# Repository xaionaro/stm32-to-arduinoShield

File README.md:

STM32 boards for fast prototyping

Original repository: [https://embed.life/dyokunev/stm32-to-arduinoShield](https://embed.life/dyokunev/stm32-to-arduinoShield)

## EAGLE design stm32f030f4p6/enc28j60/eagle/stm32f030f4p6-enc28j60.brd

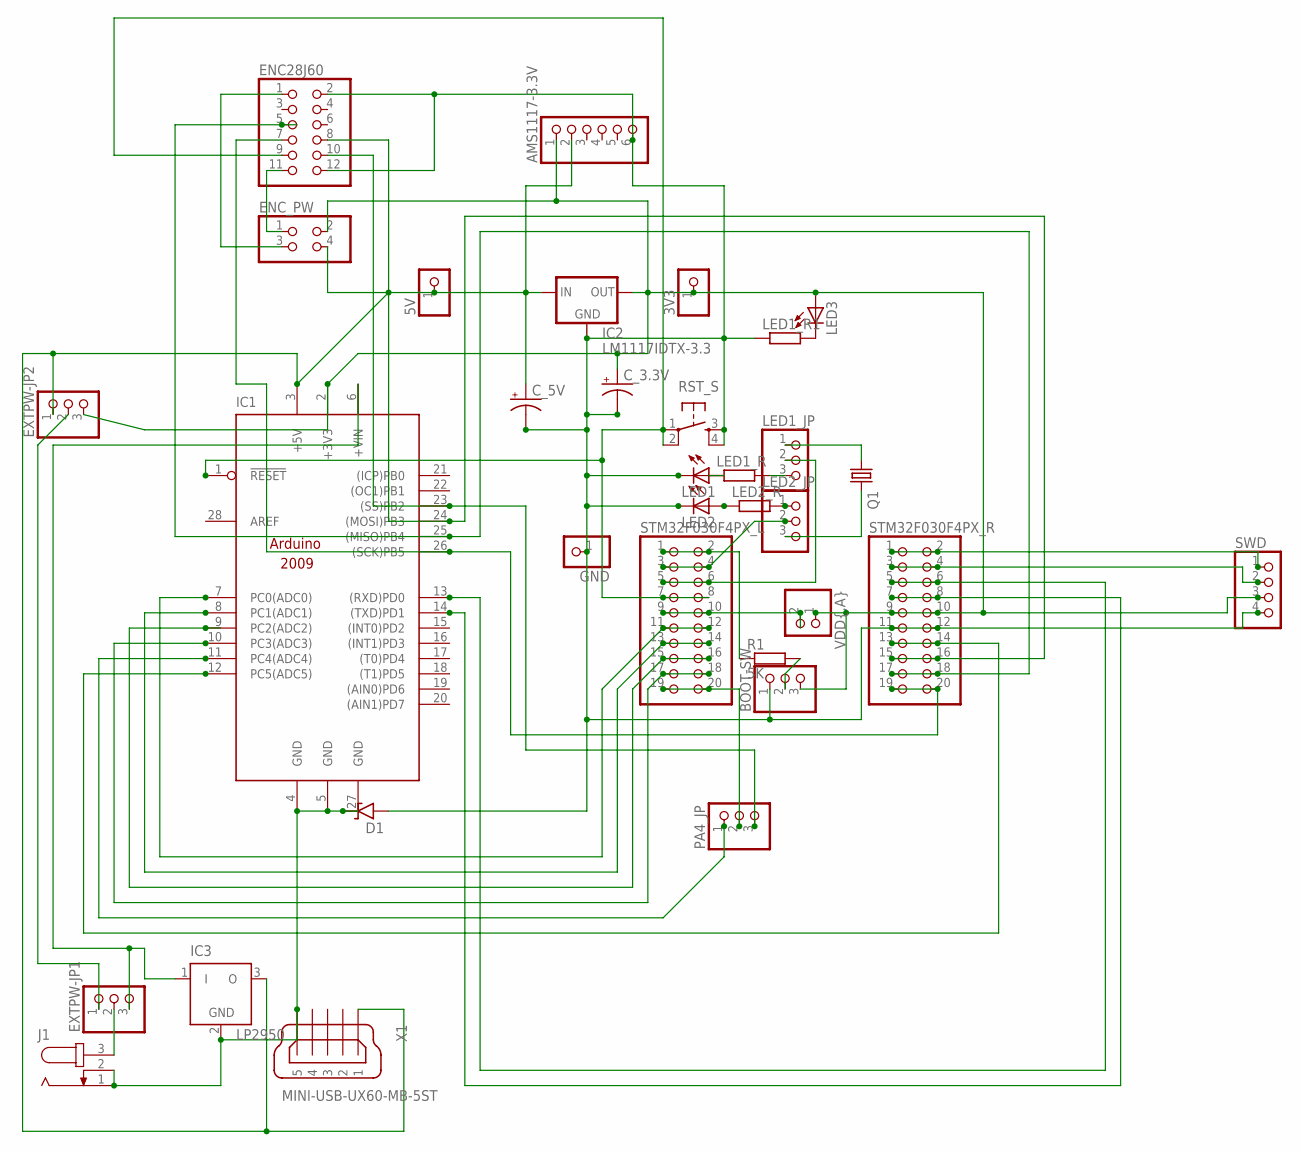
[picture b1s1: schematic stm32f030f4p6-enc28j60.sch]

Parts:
3V3, 5V: PINHD-1X1_2.00; 1X01M
AMS1117-3.3V: PINHD-1X06_2.54; 1X06
BOOT-SW: PINHD-1X3; 1X03
C_3.3V, C_5V: CPOL-USE3.5-8; E3,5-8
D1: 1N9ZENER2; DO35-2
ENC28J60: PINHD-2X6_2.54; 2X06
ENC_PW: PINHD-2X2_2.54; 2X02
EXTPW-JP1, EXTPW-JP2: PINHD-1X3; 1X03
GND: PINHD-1X1_2.00; 1X01M
IC1: ARDUINO2009_PIN_12; ARDUINO2009_2
IC2: LM1117IDTX-3.3; TO252
IC3: LP2950; DPACK
J1: JACK-PLUG0; SPC4077
LED1, LED2, LED3: LED_ELD260; LED_LD260
LED1_JP, LED2_JP: PINHD-1X3_2.54; 1X03
LED1_R, LED1_R1, LED2_R: R-EU_0204/7; 0204/7
PA4_JP: PINHD-1X3_2.54; 1X03
Q1: CRYSTALHC49S; HC49/S
R1: 5K; 0204/5
RST_S: TAC_SWITCHPTH; TACTILE-PTH
STM32F030F4PX_L, STM32F030F4PX_R: PINHD-2X10; 2X10
SWD: PINHD-1X4; 1X04
VDD{,A}: PINHD-1X2; 1X02
X1: MINI-USB-UX60-MB-5ST; UX60-MB-5ST

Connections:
3V3@EXT: ENC28J60.11, ENC_PW.1
5V: 5V.1, AMS1117-3.3V.2, C_5V.+, ENC_PW.4, EXTPW-JP2.1, IC1.3 (+5V), IC2.2 (IN), IC3.3 (O), X1.1
5V@EXT: ENC28J60.1, ENC_PW.3
BOOT: R1.1, STM32F030F4PX_L.1, STM32F030F4PX_L.2
BOOT@R: BOOT-SW.2, R1.2
GND@0: AMS1117-3.3V.6, BOOT-SW.1, C_3.3V.-, C_5V.-, D1.A, ENC28J60.2, ENC28J60.12, GND.1, IC2.1 (GND), LED1.K (C), LED1_R1.1, LED2.K (C), RST_S.3, RST_S.4, STM32F030F4PX_R.11, STM32F030F4PX_R.12, SWD.4
GND_RAW: D1.C, IC1.4 (GND), IC1.5 (GND), IC1.27 (GND), IC3.2 (GND), J1.1, J1.2, X1.5
unnamed: IC1.12 (PC5(ADC5)), STM32F030F4PX_R.13, STM32F030F4PX_R.14
unnamed: IC1.14 ((TXD)PD1), STM32F030F4PX_R.7, STM32F030F4PX_R.8
unnamed: IC1.13 ((RXD)PD0), STM32F030F4PX_R.5, STM32F030F4PX_R.6
unnamed: LED2.A, LED2_R.1
unnamed: LED1.A, LED1_R.1
unnamed: LED1_R1.2, LED3.K (C)
PA0: IC1.7 (PC0(ADC0)), STM32F030F4PX_L.11, STM32F030F4PX_L.12
PA1: IC1.8 (PC1(ADC1)), STM32F030F4PX_L.13, STM32F030F4PX_L.14
PA2: IC1.9 (PC2(ADC2)), STM32F030F4PX_L.15, STM32F030F4PX_L.16
PA3: IC1.10 (PC3(ADC3)), STM32F030F4PX_L.17, STM32F030F4PX_L.18
PA4: PA4_JP.2, STM32F030F4PX_L.19, STM32F030F4PX_L.20
PA4@L: IC1.11 (PC4(ADC4)), PA4_JP.1
PA4@R: ENC28J60.10, IC1.23 ((SS)PB2), PA4_JP.3
PA5_SCK: ENC28J60.7, IC1.26 ((SCK)PB5), STM32F030F4PX_R.19, STM32F030F4PX_R.20
PA6_MISO: ENC28J60.5, IC1.25 ((MISO)PB4), STM32F030F4PX_R.17, STM32F030F4PX_R.18
PA7_MOSI: ENC28J60.8, IC1.24 ((MOSI)PB3), STM32F030F4PX_R.15, STM32F030F4PX_R.16
PF0: LED2_JP.2, STM32F030F4PX_L.3, STM32F030F4PX_L.4
PF0@LED: LED2_JP.1, LED2_R.2
PF0@OCC: LED2_JP.3, Q1.2
PF1: LED1_JP.2, STM32F030F4PX_L.5, STM32F030F4PX_L.6
PF1@LED: LED1_JP.3, LED1_R.2
PF1@OCC: LED1_JP.1, Q1.1
RESET: ENC28J60.9, IC1.1 (!RESET), RST_S.1, RST_S.2, STM32F030F4PX_L.7, STM32F030F4PX_L.8
SWD_CLK: STM32F030F4PX_R.1, STM32F030F4PX_R.2, SWD.1
SWD_IO: STM32F030F4PX_R.3, STM32F030F4PX_R.4, SWD.2
VDD: 3V3.1, AMS1117-3.3V.1, BOOT-SW.3, C_3.3V.+, ENC_PW.2, EXTPW-JP2.3, IC1.2 (+3V3), IC2.TAB (OUT), LED3.A, STM32F030F4PX_R.9, STM32F030F4PX_R.10, SWD.3, VDD{,A}.1
VDDA: STM32F030F4PX_L.9, STM32F030F4PX_L.10, VDD{,A}.2
VIN: EXTPW-JP1.2, J1.3
VIN@HIGH: EXTPW-JP1.3, IC1.6 (+VIN), IC3.1 (I)
VIN@LOW: EXTPW-JP1.1, EXTPW-JP2.2

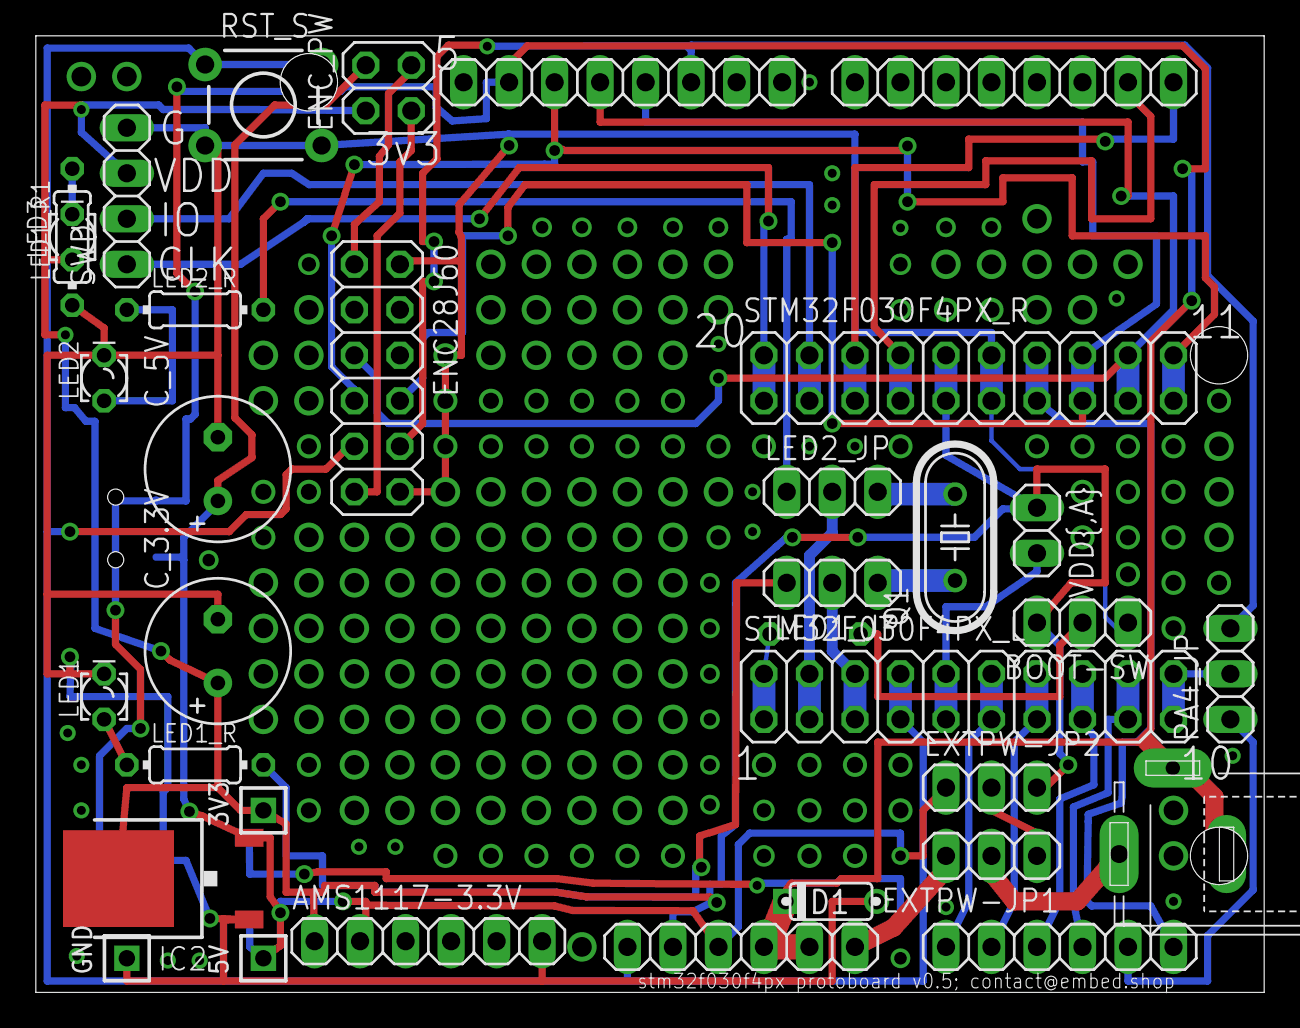
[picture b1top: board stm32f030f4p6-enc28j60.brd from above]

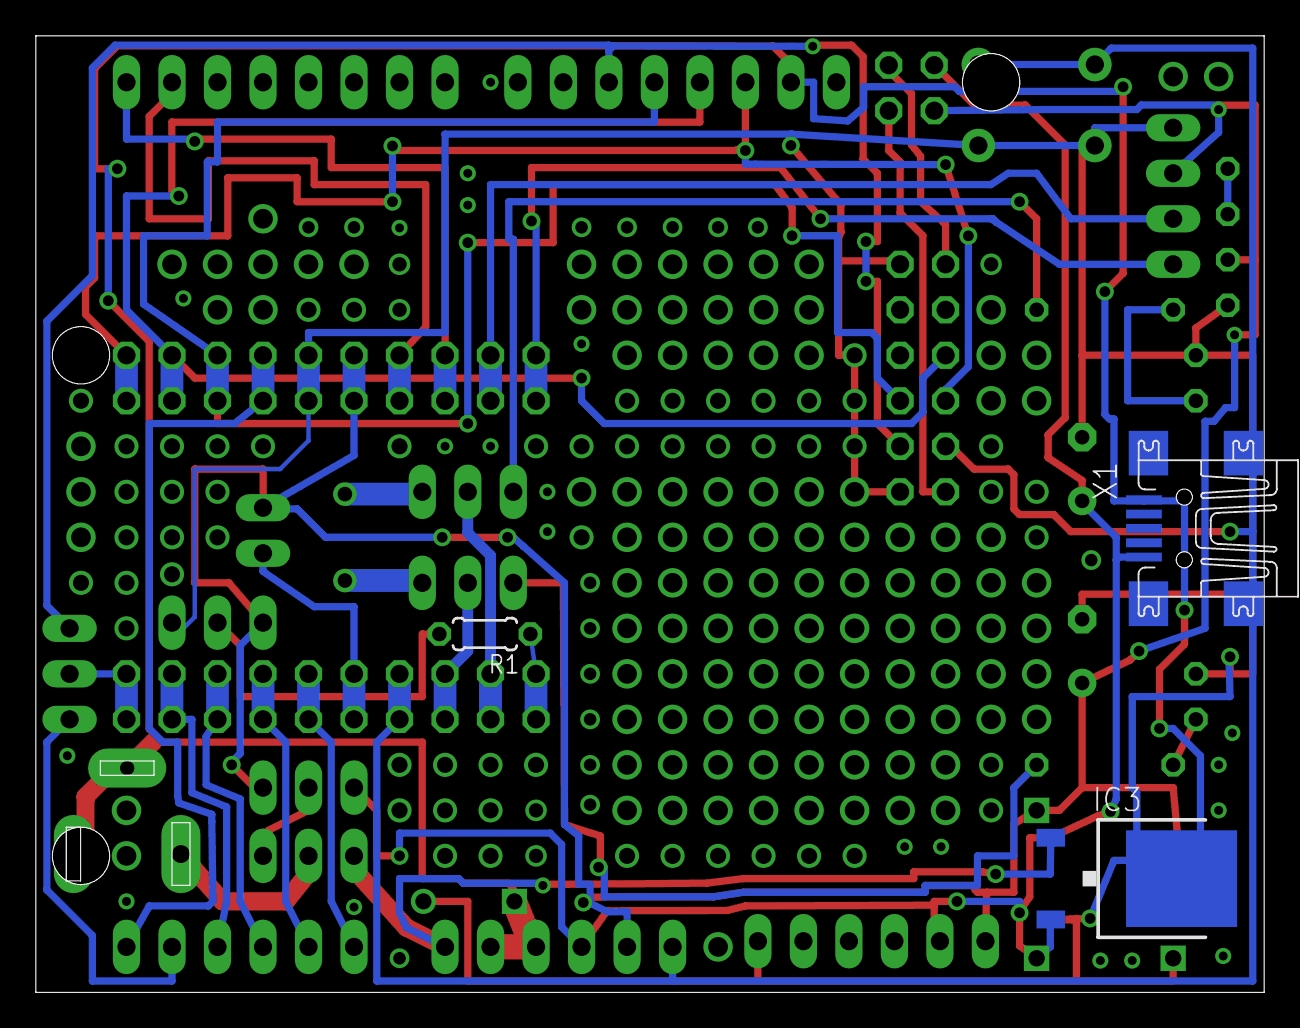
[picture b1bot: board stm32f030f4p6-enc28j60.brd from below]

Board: 2 copper layers, 68.6 x 53.4 mm, 33 parts (3 on the bottom side), 37 nets.

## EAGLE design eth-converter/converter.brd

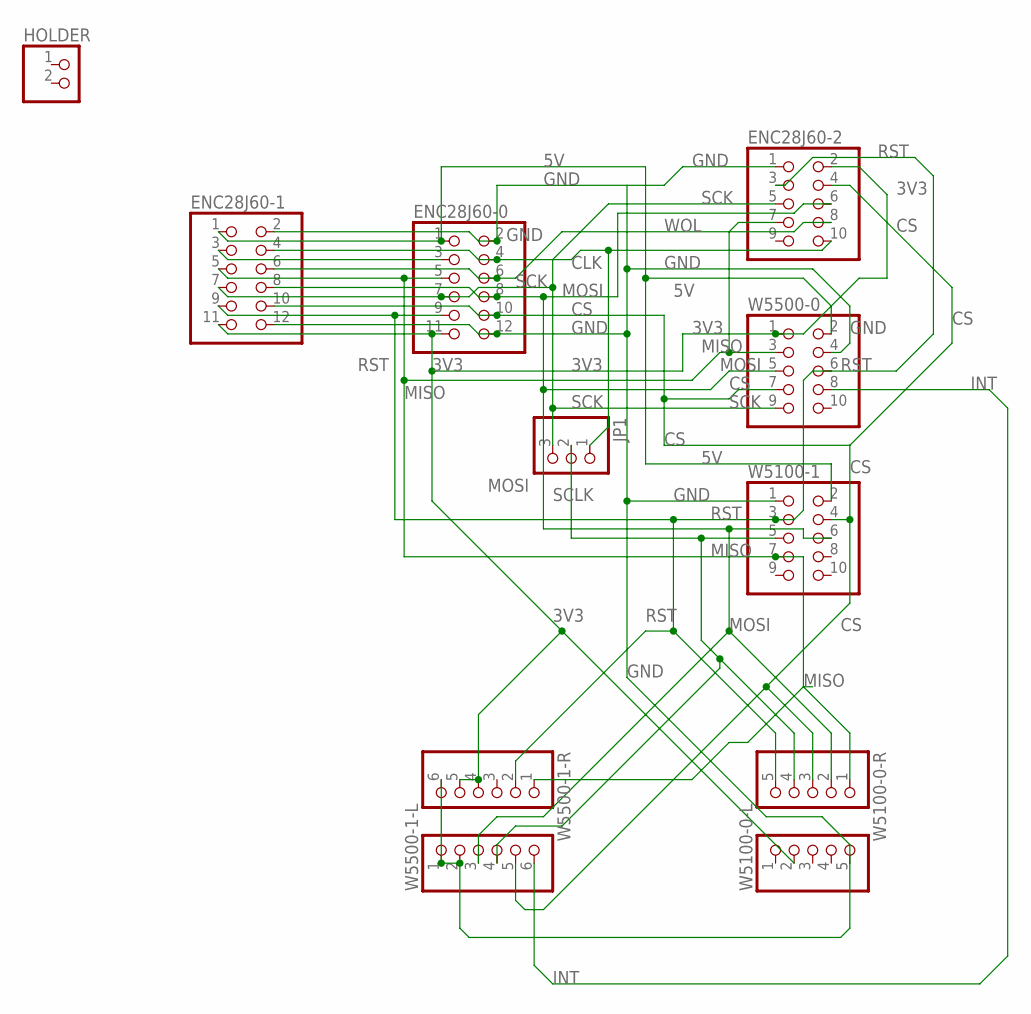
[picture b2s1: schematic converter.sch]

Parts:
ENC28J60-0, ENC28J60-1: PINHD-2X6; 2X06
ENC28J60-2: PINHD-2X5; 2X05
HOLDER: PINHD-1X2; 1X02
JP1: PINHD-1X3; 1X03
W5100-0-L, W5100-0-R: PINHD-1X5; 1X05
W5100-1, W5500-0: PINHD-2X5; 2X05
W5500-1-L, W5500-1-R: PINHD-1X6; 1X06

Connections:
3V3: ENC28J60-0.11, ENC28J60-1.11, ENC28J60-2.2, W5100-0-L.2, W5500-0.1, W5500-1-R.4, W5500-1-R.5
5V: ENC28J60-0.1, ENC28J60-1.1, W5100-1.2, W5500-0.2
CLK: ENC28J60-0.4, ENC28J60-1.4, ENC28J60-2.10, JP1.1
CS: ENC28J60-0.10, ENC28J60-1.10, ENC28J60-2.4, W5100-0-R.3, W5100-1.4, W5500-0.7, W5500-1-L.5
GND: ENC28J60-0.2, ENC28J60-0.12, ENC28J60-1.2, ENC28J60-1.12, ENC28J60-2.1, W5100-0-L.5, W5100-1.1, W5500-0.4, W5500-1-L.1, W5500-1-L.2, W5500-1-R.6
INT: W5500-0.8, W5500-1-L.6
MISO: ENC28J60-0.5, ENC28J60-1.5, ENC28J60-2.7, W5100-0-R.1, W5100-1.7, W5500-0.3
MOSI: ENC28J60-0.8, ENC28J60-1.8, ENC28J60-2.6, W5100-0-R.2, W5100-1.6, W5500-0.5, W5500-1-L.3
unnamed: ENC28J60-0.3, ENC28J60-1.3
RST: ENC28J60-0.9, ENC28J60-1.9, ENC28J60-2.3, W5100-0-R.5, W5100-1.3, W5500-0.6, W5500-1-R.2
SCK: ENC28J60-0.7, ENC28J60-1.7, ENC28J60-2.5, JP1.3, W5500-0.9
SCLK: JP1.2, W5100-0-R.4, W5100-1.5, W5500-1-L.4
WOL: ENC28J60-0.6, ENC28J60-1.6, ENC28J60-2.8

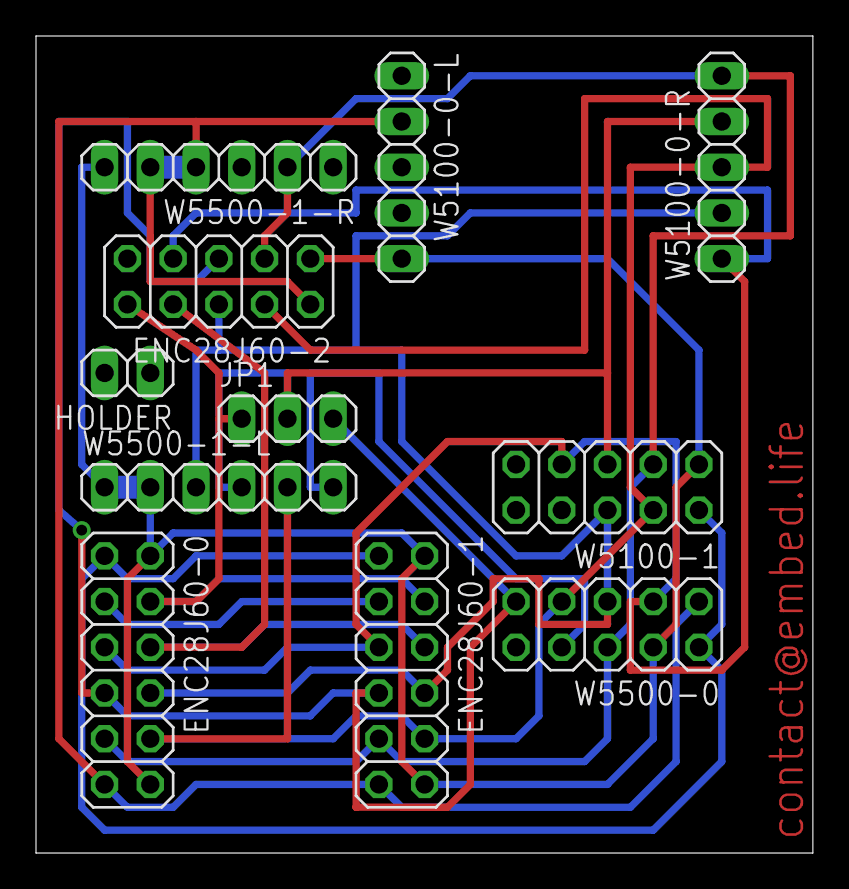
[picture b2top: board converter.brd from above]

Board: 2 copper layers, 43.2 x 45.4 mm, 11 parts (0 on the bottom side), 13 nets.

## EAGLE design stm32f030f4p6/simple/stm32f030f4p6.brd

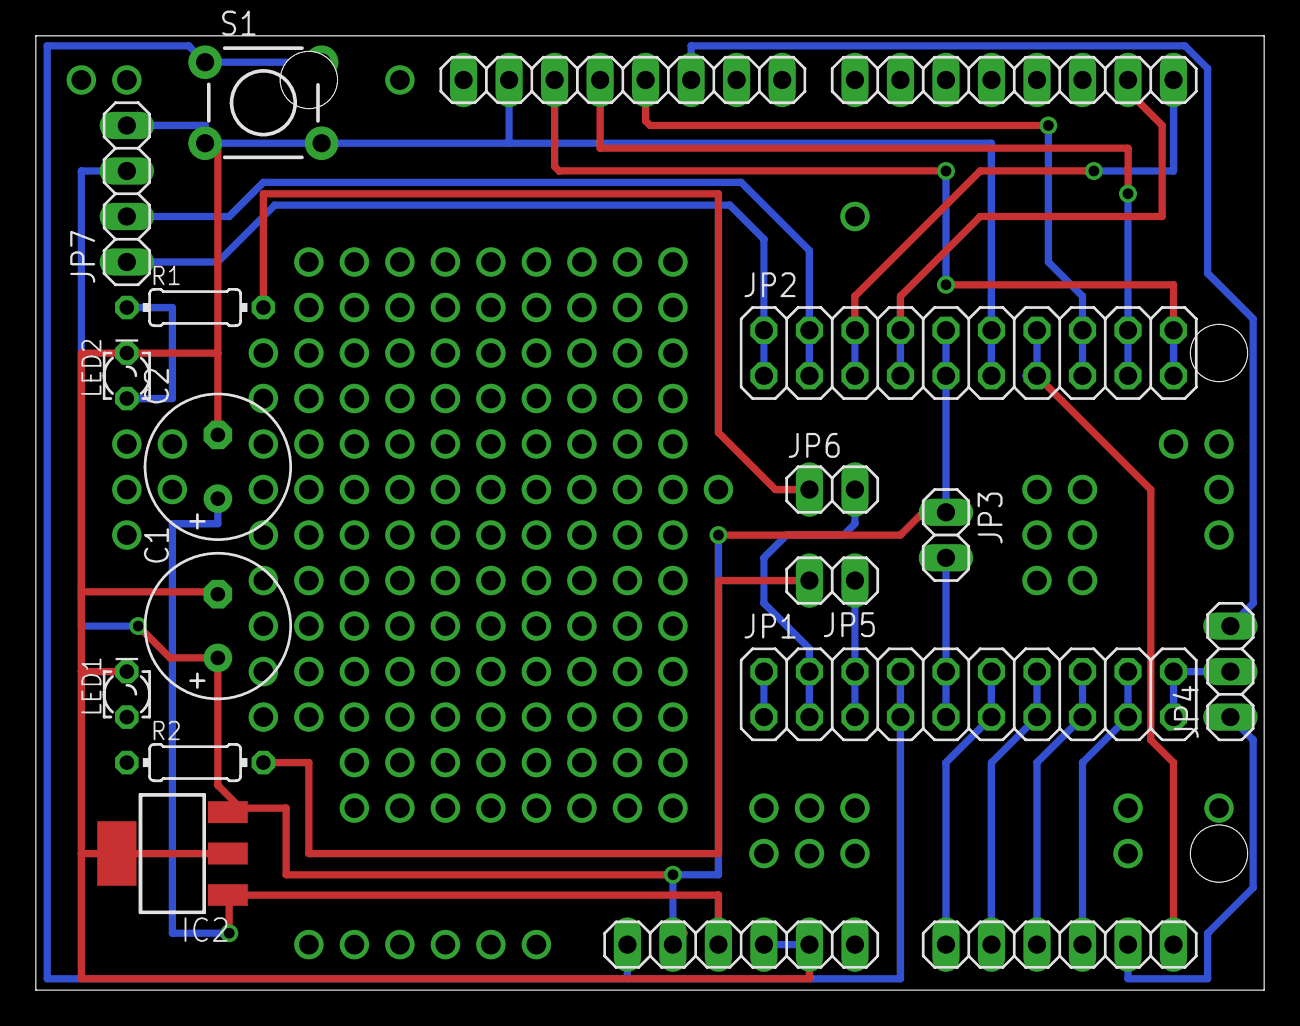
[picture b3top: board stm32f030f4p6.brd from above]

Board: 2 copper layers, 68.6 x 53.3 mm, 16 parts (0 on the bottom side), 27 nets.

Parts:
C1, C2: E3,5-8
IC1: ARDUINO2009_2
IC2: SOT223
JP1, JP2: 2X10
JP3, JP5, JP6: 1X02
JP4: 1X03
JP7: 1X04
LED1, LED2: LED_LD260
R1, R2: 0204/7
S1: TACTILE-PTH

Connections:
unnamed: JP1.9, JP1.10, JP3.2
unnamed: JP1.1, JP1.2
unnamed: JP1.3, JP1.4, JP6.2
unnamed: JP1.5, JP1.6, JP5.1
unnamed: JP1.19, JP1.20, JP4.2
unnamed: IC1.7, JP1.11, JP1.12
unnamed: IC1.8, JP1.13, JP1.14
unnamed: IC1.9, JP1.15, JP1.16
unnamed: IC1.10, JP1.17, JP1.18
unnamed: IC1.11, JP4.1
unnamed: IC1.26, JP2.19, JP2.20
unnamed: IC1.25, JP2.17, JP2.18
unnamed: IC1.24, JP2.15, JP2.16
unnamed: IC1.12, JP2.13, JP2.14
unnamed: IC1.14, JP2.7, JP2.8
unnamed: IC1.13, JP2.5, JP2.6
unnamed: JP2.3, JP2.4, JP7.2
unnamed: JP2.1, JP2.2, JP7.1
unnamed: IC1.1, JP1.7, JP1.8, S1.1, S1.2
unnamed: C1.-, C2.-, IC1.4, IC1.5, IC1.27, IC2.2, JP2.11, JP2.12, JP7.4, LED1.K, LED2.K, S1.3, S1.4
unnamed: IC1.23, JP4.3
unnamed: C2.+, IC1.3, IC2.1
unnamed: C1.+, IC1.2, IC2.3, JP2.9, JP2.10, JP3.1, JP7.3
unnamed: LED2.A, R1.1
unnamed: LED1.A, R2.1
unnamed: JP5.2, R2.2
unnamed: JP6.1, R1.2

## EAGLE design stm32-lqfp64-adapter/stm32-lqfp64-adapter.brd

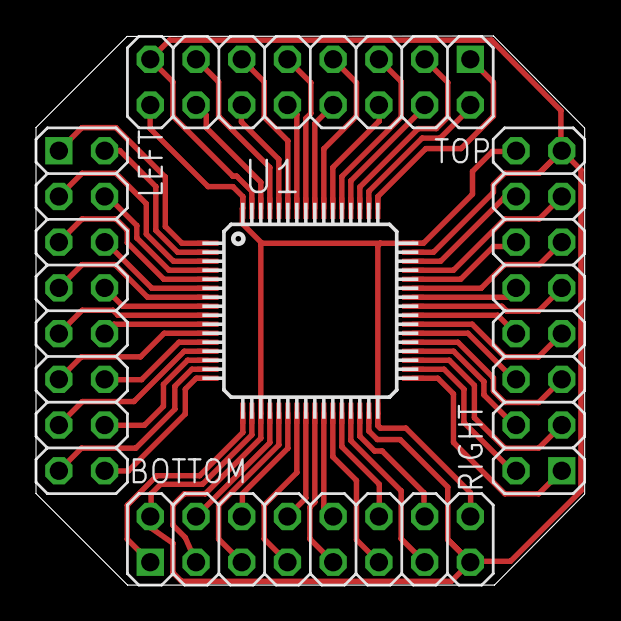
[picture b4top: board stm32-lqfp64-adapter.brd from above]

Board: 2 copper layers, 30.5 x 30.5 mm, 5 parts (0 on the bottom side), 58 nets.

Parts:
BOTTOM: 2X08
LEFT: 2X08
RIGHT: 2X08
TOP: 2X08
U1: STM32F10XRXT6; TQFP64

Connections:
unnamed: LEFT.1, U1.1
unnamed: LEFT.12, U1.12
unnamed: LEFT.13, U1.13
unnamed: LEFT.5, U1.5
unnamed: LEFT.6, U1.6
unnamed: TOP.6, U1.54
unnamed: LEFT.7, U1.7
unnamed: TOP.12, U1.60
unnamed: LEFT.2, U1.2
unnamed: LEFT.3, U1.3
unnamed: LEFT.4, U1.4
unnamed: LEFT.8, U1.8
unnamed: LEFT.9, U1.9
unnamed: LEFT.10, U1.10
unnamed: LEFT.11, U1.11
unnamed: LEFT.14, U1.14
unnamed: LEFT.15, U1.15
unnamed: LEFT.16, U1.16
unnamed: BOTTOM.1, U1.17
unnamed: BOTTOM.8, U1.24
unnamed: BOTTOM.2, BOTTOM.15, RIGHT.15, TOP.15, U1.18, U1.31, U1.47, U1.63
unnamed: BOTTOM.3, BOTTOM.16, RIGHT.16, TOP.16, U1.19, U1.32, U1.48, U1.64
unnamed: BOTTOM.4, U1.20
unnamed: BOTTOM.5, U1.21
unnamed: BOTTOM.6, U1.22
unnamed: BOTTOM.7, U1.23
unnamed: BOTTOM.9, U1.25
unnamed: BOTTOM.10, U1.26
unnamed: BOTTOM.11, U1.27
unnamed: BOTTOM.12, U1.28
unnamed: BOTTOM.13, U1.29
unnamed: BOTTOM.14, U1.30
unnamed: RIGHT.1, U1.33
unnamed: RIGHT.2, U1.34
unnamed: RIGHT.3, U1.35
unnamed: RIGHT.4, U1.36
unnamed: RIGHT.5, U1.37
unnamed: RIGHT.6, U1.38
unnamed: RIGHT.7, U1.39
unnamed: RIGHT.8, U1.40
unnamed: TOP.3, U1.51
unnamed: RIGHT.9, U1.41
unnamed: RIGHT.10, U1.42
unnamed: RIGHT.11, U1.43
unnamed: RIGHT.12, U1.44
unnamed: RIGHT.13, U1.45
unnamed: RIGHT.14, U1.46
unnamed: TOP.1, U1.49
unnamed: TOP.2, U1.50
unnamed: TOP.4, U1.52
unnamed: TOP.5, U1.53
unnamed: TOP.13, U1.61
unnamed: TOP.14, U1.62
unnamed: TOP.11, U1.59
unnamed: TOP.10, U1.58
unnamed: TOP.9, U1.57
unnamed: TOP.8, U1.56
unnamed: TOP.7, U1.55

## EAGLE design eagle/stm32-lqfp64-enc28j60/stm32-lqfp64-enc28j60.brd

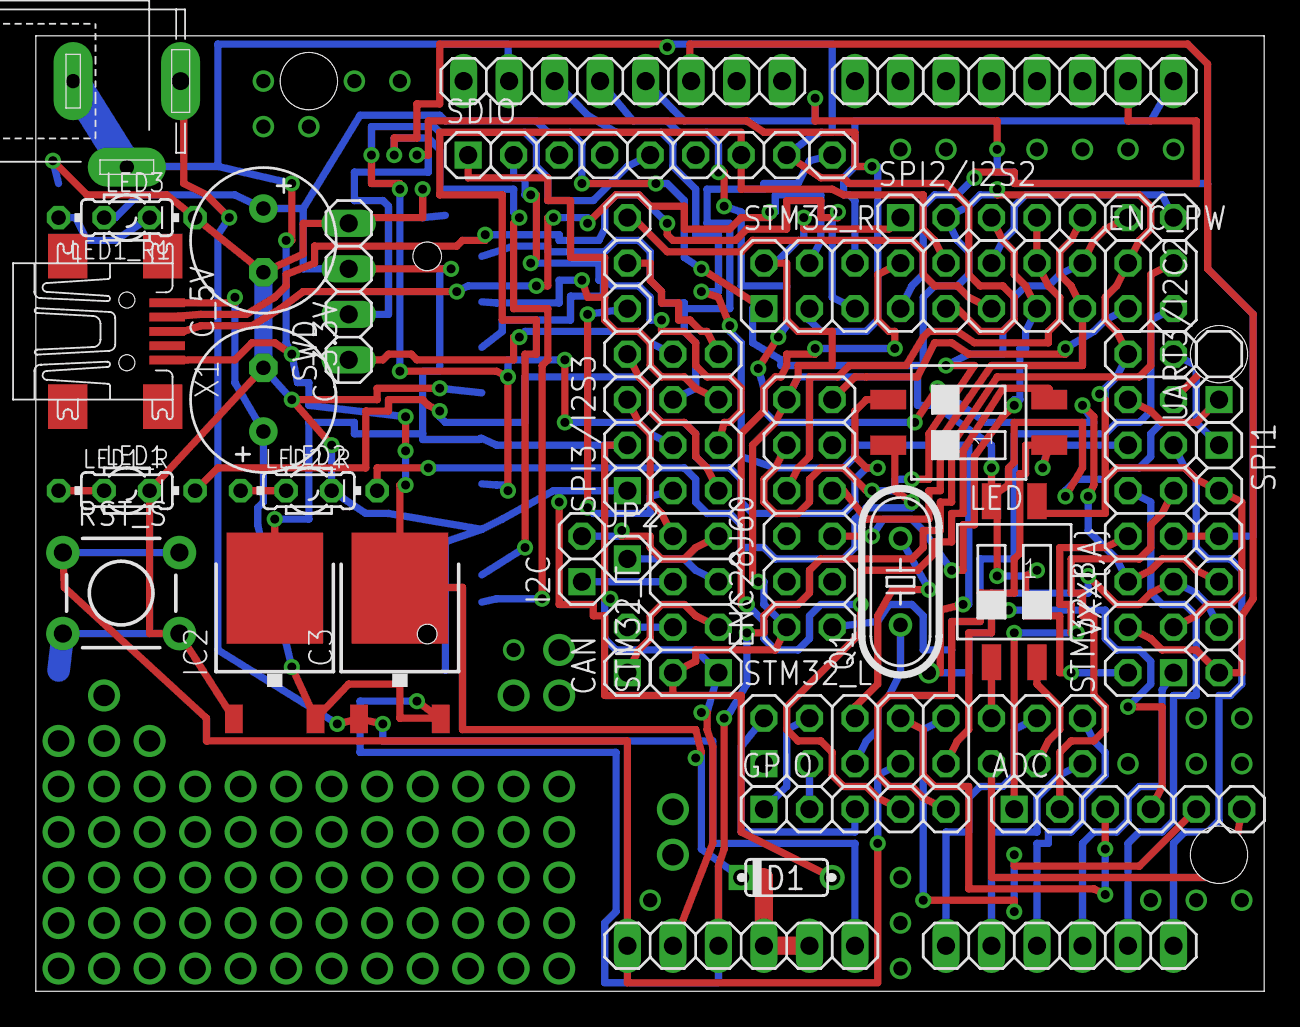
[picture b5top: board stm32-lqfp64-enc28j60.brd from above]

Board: 2 copper layers, 68.6 x 53.3 mm, 36 parts (1 on the bottom side), 67 nets.

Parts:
ADC: 1X06-S
CAN: 1X02-S
C_3.3V, C_5V: E3,5-8
D1: DO35-2
ENC28J60: 2X06
ENC_PW: 2X02
GPIO: 1X05-S
I2C: 1X02-S
IC1: ARDUINO2009_2
IC2: LM1117IDTX-3.3; TO252
IC3: LP2950; DPACK
J1: SPC4077
JP2: 1X01-S
LED: SWS002; SMS-002
LED1, LED2, LED3: LED_LD260
LED1_R, LED1_R1, LED2_R: 0204/7
Q1: HC49/S
RST_S: TACTILE-PTH
SDIO: 1X09-S
SPI1: 1X06-S
SPI2/I2S2, SPI3/I2S3: 1X07-S
STM32_B, STM32_L, STM32_R, STM32_T: 2X08
SWD: 1X04
U$2: SDCMF-10915W010
UART3/I2C2: 1X02-S
VXX{,A}: SWS002; SMS-002
X1: MINI-USB-UX60-MB-5ST; UX60-MB-5ST

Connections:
5V: C_5V.+, ENC_PW.4, IC1.3, IC2.2, IC3.3, X1.1
ADC1: IC1.8, STM32_L.15
ADC2: IC1.9, STM32_L.16
ADC3: IC1.10, STM32_B.1
ADC4: IC1.11, STM32_B.10
ADC5: IC1.12, STM32_B.11
ADC_0: IC1.7, STM32_L.14
GND: C_3.3V.-, C_5V.-, D1.A, ENC28J60.2, ENC28J60.12, IC2.1, LED1.K, LED1_R1.1, LED2.K, RST_S.3, RST_S.4, SPI1.1, SPI2/I2S2.1, SPI3/I2S3.1, STM32_B.2, STM32_B.15, STM32_R.2, STM32_T.2, SWD.4, U$2.3, U$2.6, U$2.12, U$2.13, U$2.14, U$2.15, VXX{,A}.2
GND_RAW: D1.C, IC1.4, IC1.5, IC1.27, IC3.2, J1.1, J1.2, X1.5
GPIO_FREE1: GPIO.3, STM32_L.2
GPIO_FREE2: GPIO.2, STM32_L.3
GPIO_FREE3: GPIO.1, STM32_L.4
GPIO_FREE4: GPIO.5, LED.1, STM32_B.12
I2C1_SCL: I2C.2, STM32_T.7
I2C1_SDA: I2C.1, STM32_T.6
unnamed: SPI3/I2S3.7, STM32_R.11
unnamed: CAN.1, STM32_T.3
unnamed: CAN.2, STM32_T.4
unnamed: JP2.1, STM32_T.5
unnamed: STM32_L.13, VXX{,A}.4
unnamed: STM32_L.12, VXX{,A}.3
unnamed: SPI3/I2S3.3, STM32_T.8
unnamed: SPI3/I2S3.4, STM32_T.9
unnamed: SPI3/I2S3.5, STM32_T.10
unnamed: ADC.1, STM32_B.8
unnamed: ADC.3, STM32_L.8
unnamed: ADC.2, STM32_B.9
unnamed: LED.3, LED1_R.2
unnamed: ADC.4, STM32_L.9
unnamed: ADC.5, STM32_L.10
unnamed: ADC.6, STM32_L.11
unnamed: STM32_B.13, UART3/I2C2.2
unnamed: STM32_B.14, UART3/I2C2.1
unnamed: SPI3/I2S3.6, STM32_T.15
unnamed: SPI2/I2S2.7, STM32_R.12
unnamed: IC1.13, STM32_R.6
unnamed: SDIO.5, STM32_T.12, U$2.5
unnamed: IC1.6, IC3.1, J1.3
unnamed: LED2.A, LED2_R.1
unnamed: LED1.A, LED1_R.1
unnamed: LED.4, LED2_R.2
unnamed: GPIO.4, LED.2, STM32_R.8
unnamed: IC1.14, STM32_R.7
unnamed: STM32_R.5, X1.2
unnamed: STM32_R.4, X1.3
unnamed: ENC28J60.1, ENC_PW.3
unnamed: ENC28J60.11, ENC_PW.1
unnamed: LED1_R1.2, LED3.K
RCC_OSC_IN: Q1.1, STM32_L.5
RCC_OSC_OUT: Q1.2, STM32_L.6
RST: IC1.1, RST_S.1, RST_S.2, STM32_L.7
SDIO_CMD: SDIO.2, STM32_T.11, U$2.2
SDIO_D0: SDIO.7, STM32_R.10, U$2.7
SDIO_D1: SDIO.8, STM32_R.9, U$2.8
SDIO_D2: SDIO.9, STM32_T.14, U$2.9
SDIO_D3: SDIO.1, STM32_T.13, U$2.1
SPI1_MISO: IC1.25, SPI1.4, STM32_B.6
SPI1_MOSI: IC1.24, SPI1.3, STM32_B.7
SPI1_NSS: IC1.23, SPI1.6, STM32_B.4
SPI1_SCK: IC1.26, SPI1.5, STM32_B.5
SPI2_MISO: ENC28J60.8, SPI2/I2S2.4, STM32_R.14
SPI2_MOSI: ENC28J60.5, SPI2/I2S2.3, STM32_R.13
SPI2_NSS: ENC28J60.10, SPI2/I2S2.6, STM32_R.16
SPI2_SCK: ENC28J60.7, SPI2/I2S2.5, STM32_R.15
SWD_CLK: STM32_T.16, SWD.1
SWD_IO: STM32_R.3, SWD.2
VDD: C_3.3V.+, ENC_PW.2, IC1.2, IC2.TAB, LED3.A, SPI1.2, SPI2/I2S2.2, SPI3/I2S3.2, STM32_B.3, STM32_B.16, STM32_R.1, STM32_T.1, SWD.3, U$2.4, VXX{,A}.1

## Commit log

2016-08-19 Initial commit, pt.2
2016-08-19 Initial commit, pt.3
2016-08-30 Dimensions fixes
2016-09-01 Added gerber files for stm32f030f4p6/enc28j60
2017-04-15 updated stm32f030f4p6/enc28j60/eagle
2017-04-15 fixed 473b0256177802d8c32fc4b0b20f1561cfde31d8
2017-04-16 Connected enc28j60 RST in stm32f030f4p6/enc28j60/eagle
2017-04-16 Fixed MISO-MOSI
2017-04-16 Added initial README.md
